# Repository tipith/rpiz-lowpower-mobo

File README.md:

# Motherboard

Purpose of this PCB is have a low-power way of sending SMS messages once an external trigger is detected. For example, it can be used as a an detector for door open events.

Features
- 18650 battery holder
- Attiny1604 power manager
- External trigger connector
- Nokia phone connector (FBUS + battery size indicator + battery temp)
- 2-way communication between PM and RPi

# Power manager (attiny1604)

tbd

# SMS sender (RPi Zero)

## Instructions

- /boot
   - add file: sshe
   - add file: wpa_supplicant.conf
   - add file: trapsms.ini
- /boot/config.txt
   - add "dtoverlay rpi3-disable-bt"
   - uncomment and modify "dtparam=i2c_arm=on,i2c_arm_baudrate=50000"
-  /boot/cmdline.txt
   - remove "console=serial0,115200 console=tty1"
- shell commands
   - sudo systemctl disable hciuart
   - sudo apt update && sudo apt upgrade
   - sudo apt install git gammu python3-gammu
- install pigpio
  - sudo apt-get install pigpio
  - wget https://raw.githubusercontent.com/joan2937/pigpio/master/util/pigpiod.service
  - sudo cp pigpiod.service /etc/systemd/system
  - sudo systemctl enable pigpiod.service
  - sudo systemctl start pigpiod.service
- run
   - python3 rpi_smssender/sms_sender.py

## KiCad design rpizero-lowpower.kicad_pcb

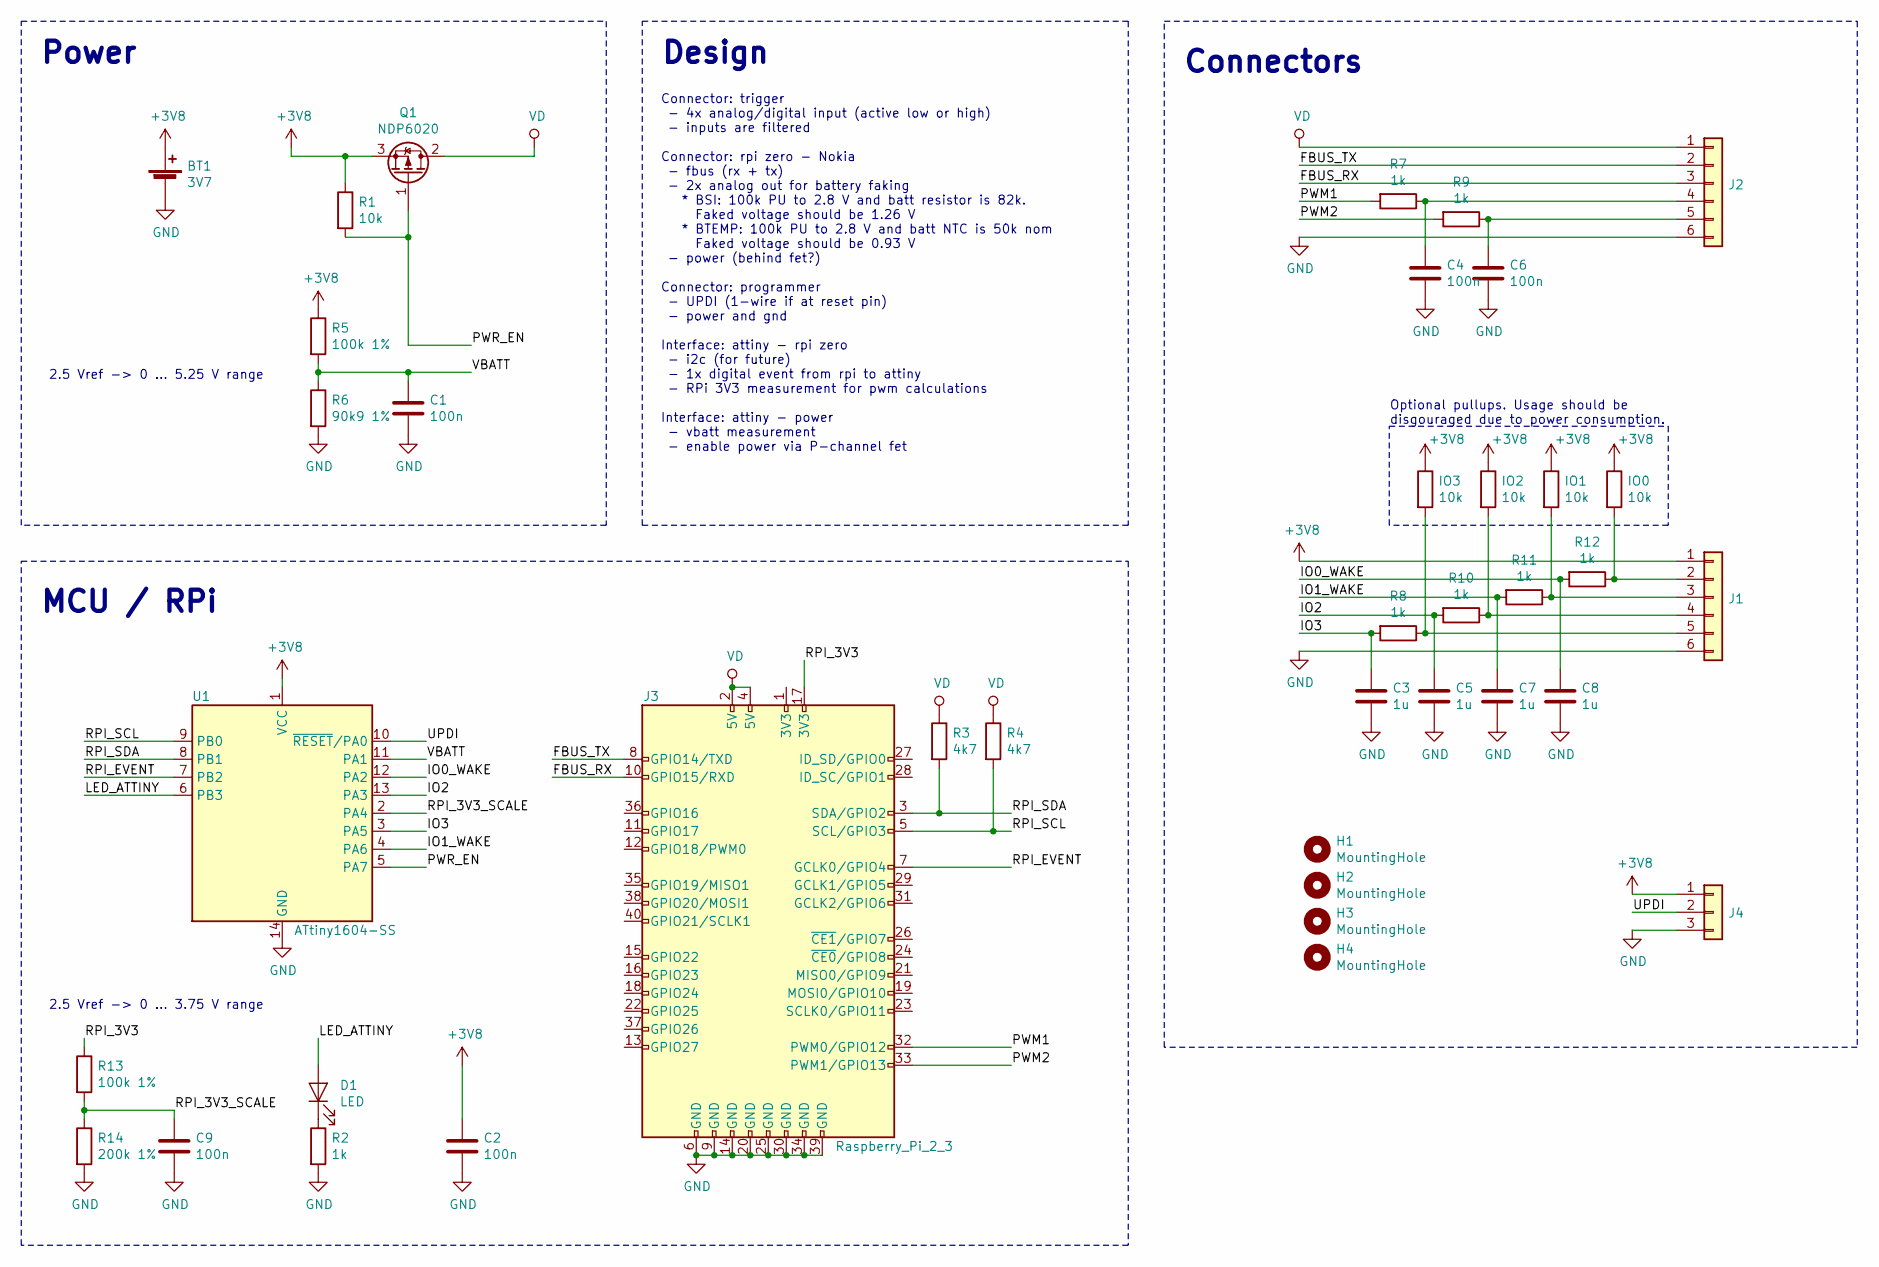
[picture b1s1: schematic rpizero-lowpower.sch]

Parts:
BT1: 3V7; 18650-ebay
C1, C2, C4, C6, C9: 100n; C_0805_2012Metric_Pad1.15x1.40mm_HandSolder
C3, C5, C7, C8: 1u; C_0805_2012Metric_Pad1.15x1.40mm_HandSolder
D1: LED; LED_0805_2012Metric_Pad1.15x1.40mm_HandSolder
H1, H2, H3, H4: MountingHole; MountingHole_5.3mm__no_courtyard
IO0, IO1, IO2, IO3: 10k; R_0805_2012Metric_Pad1.15x1.40mm_HandSolder
J1: Screw_Terminal_01x06; PinHeader_2x03_P2.54mm_Vertical
J2: Screw_Terminal_01x04; PinHeader_2x03_P2.54mm_Vertical
J3: Raspberry_Pi_2_3; Raspberry_Pi_Zero_Socketed_THT_FaceDown_MountingHoles_no_co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
J4: Conn_01x03; PinHeader_1x03_P2.54mm_Vertical
Q1: NDP6020; TO-220-3_Horizontal_TabDown
R1: 10k; R_0805_2012Metric_Pad1.15x1.40mm_HandSolder
R2, R7, R8, R9, R10, R11, R12: 1k; R_0805_2012Metric_Pad1.15x1.40mm_HandSolder
R3, R4: 4k7; R_0805_2012Metric_Pad1.15x1.40mm_HandSolder
R5, R13: 100k 1%; R_0805_2012Metric_Pad1.15x1.40mm_HandSolder
R6: 90k9 1%; R_0805_2012Metric_Pad1.15x1.40mm_HandSolder
R14: 200k 1%; R_0805_2012Metric_Pad1.15x1.40mm_HandSolder
U1: ATtiny1604-SS; SOIC-14_3.9x8.7mm_P1.27mm

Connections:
+3V8: BT1.1 (+), C2.1, IO0.1, IO1.1, IO2.1, IO3.1, J1.1, J4.1, Q1.3 (S), R1.1, R5.1, U1.1 (VCC)
/FBUS_RX: J2.3, J3.10 (GPIO15/RXD)
/FBUS_TX: J2.2, J3.8 (GPIO14/TXD)
/IO0_WAKE: C8.1, R12.2, U1.12 (PA2)
/IO1_WAKE: C7.1, R11.2, U1.4 (PA6)
/IO2: C5.1, R10.2, U1.13 (PA3)
/IO3: C3.1, R8.2, U1.3 (PA5)
/LED_ATTINY: D1.2 (A), U1.6 (PB3)
/PWM1: J3.32 (PWM0/GPIO12), R7.2
/PWM2: J3.33 (PWM1/GPIO13), R9.2
/PWR_EN: Q1.1 (G), R1.2, U1.5 (PA7)
/RPI_3V3: J3.17 (3V3), R13.1
/RPI_3V3_SCALE: C9.1, R13.2, R14.1, U1.2 (PA4)
/RPI_EVENT: J3.7 (GCLK0/GPIO4), U1.7 (PB2)
/RPI_SCL: J3.5 (SCL/GPIO3), R4.2, U1.9 (PB0)
/RPI_SDA: J3.3 (SDA/GPIO2), R3.2, U1.8 (PB1)
/UPDI: J4.2, U1.10 (~RESET~/PA0)
/VBATT: C1.1, R5.2, R6.1, U1.11 (PA1)
GND: BT1.2 (-), C1.2, C2.2, C3.2, C4.2, C5.2, C6.2, C7.2, C8.2, C9.2, J1.6, J2.6, J3.6 (GND), J3.9 (GND), J3.14 (GND), J3.20 (GND), J3.25 (GND), J3.30 (GND), J3.34 (GND), J3.39 (GND), J4.3, R2.2, R6.2, R14.2, U1.14 (GND)
unnamed: C4.1, J2.4, R7.1
unnamed: C6.1, J2.5, R9.1
unnamed: D1.1 (K), R2.1
unnamed: IO0.2, J1.2, R12.1
unnamed: IO1.2, J1.3, R11.1
unnamed: IO2.2, J1.4, R10.1
unnamed: IO3.2, J1.5, R8.1
VD: J2.1, J3.2 (5V), J3.4 (5V), Q1.2 (D), R3.1, R4.1

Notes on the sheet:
Connector: trigger - 4x analog/digital input (active low or high) - inputs are filtered Connector: rpi zero - Nokia - fbus (rx + tx) - 2x analog out for battery faking * BSI: 100k PU to 2.8 V and batt resistor is 82k. Faked voltage should be 1.26 V * BTEMP: 100k PU to 2.8 V and batt NTC is 50k nom 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
Power
MCU / RPi
Connectors
Design
Optional pullups. Usage should be disgouraged due to power consumption.
2.5 Vref -> 0 ... 5.25 V range
2.5 Vref -> 0 ... 3.75 V range

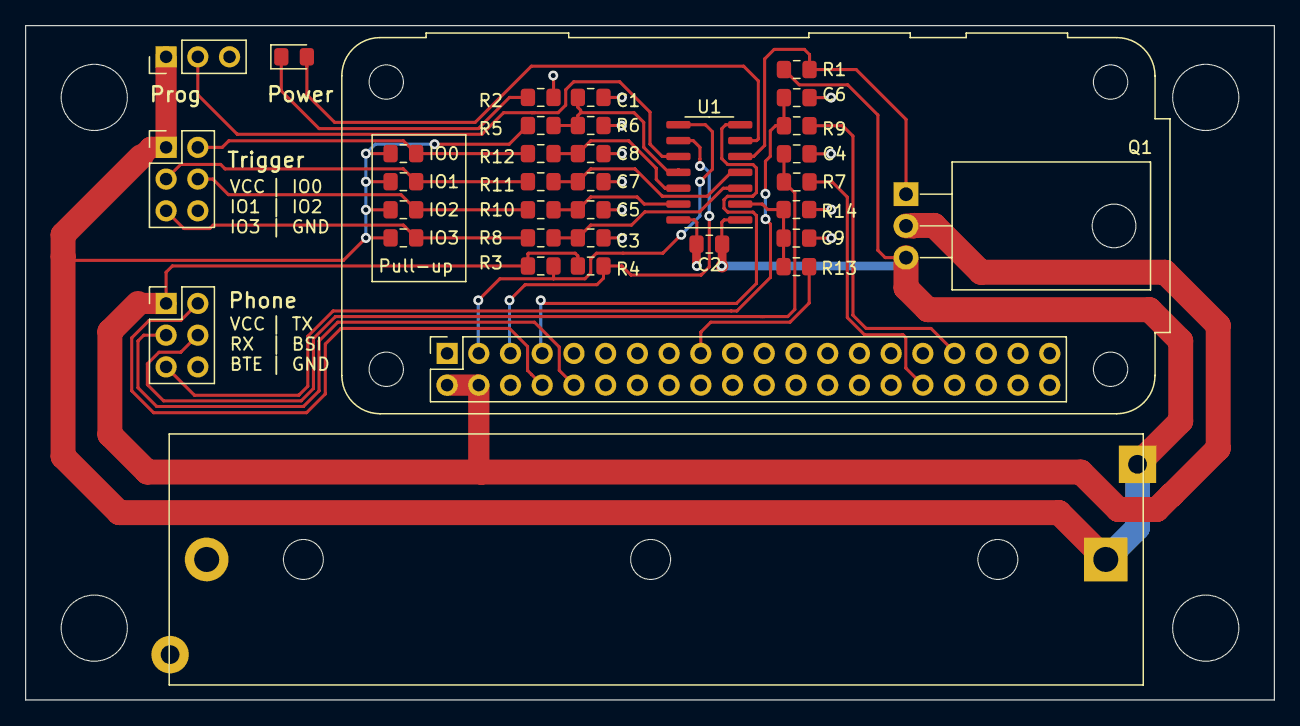
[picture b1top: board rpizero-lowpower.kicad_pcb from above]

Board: 2 copper layers, 100.0 x 54.0 mm, 39 parts (0 on the bottom side), 27 nets.

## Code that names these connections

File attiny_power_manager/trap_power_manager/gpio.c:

/*
 * io.c
 *
 * Created: 30/06/2019 21.23.41
 *  Author: pihlstro
 */ 
#include <avr/io.h>
#include <avr/interrupt.h>

#include "gpio.h"

struct gpio_context {
	onPinTransitionFunc cb;
};

static struct gpio_context gpio[PIN_NUM];

ISR(PORTA_PORT_vect)
{
	if (PORTA.INTFLAGS & PORT_INT2_bm)
	{
		PORTA.INTFLAGS = PORT_INT2_bm;
		if (gpio[PIN_IO0].cb)
		{
			gpio[PIN_IO0].cb();
		}
	}
	
	if (PORTA.INTFLAGS & PORT_INT6_bm)
	{
		PORTA.INTFLAGS = PORT_INT6_bm;
		if (gpio[PIN_IO1].cb)
		{
			gpio[PIN_IO1].cb();
		}
	}
	
	reti();
}

ISR(PORTB_PORT_vect)
{
	if (PORTA.INTFLAGS & PORT_INT2_bm)
	{
		PORTA.INTFLAGS = PORT_INT2_bm;
		if (gpio[PIN_RPI_EVENT].cb)
		{
			gpio[PIN_RPI_EVENT].cb();
		}
	}
	
	reti();
}

void gpio_init(void)
{
	/* PA0 - UPDI
	 * PA1 - VBATT    - analog in
	 * PA2 - IO0_WAKE - digital in, async isr 
	 * PA3 - IO2      - digital in/out
	 * PA4 - RPI_3V3  - analog in
	 * PA5 - IO3      - digital in/out
	 * PA6 - IO1_WAKE - digital in, async isr
	 * PA7 - PWR_EN   - digital out */
	PORTA.DIRSET = 0b10101000;
	PORTA.PIN1CTRL = PORT_ISC_INPUT_DISABLE_gc;
	PORTA.PIN2CTRL = PORT_ISC_FALLING_gc;
	PORTA.PIN3CTRL = PORT_ISC_INPUT_DISABLE_gc;
	PORTA.PIN6CTRL = PORT_ISC_FALLING_gc;
	
	/* PB0 - RPI_SCL   - i2c slave
	 * PB1 - RPI_SCA   - i2c slave
	 * PB2 - RPI_EVENT - digital in, async isr
	 * PB3 - LED       - digital out */
	PORTB.DIRSET = 0b1011;
	PORTB.PIN2CTRL = PORT_ISC_FALLING_gc;
}

void gpio_subscribe(enum iopin pin, onPinTransitionFunc cb)
{
	gpio[pin].cb = cb;
}

void gpio_set(enum iopin pin)
{
	switch (pin)
	{
	case PIN_IO2:
		PORTA.OUTSET = (1 << 3);
		break;
	case PIN_IO3:
		PORTA.OUTSET = (1 << 5);
		break;
	case PIN_PWR_EN:
		PORTA.OUTSET = (1 << 7);
		break;
	case PIN_LED:
		PORTB.OUTSET = (1 << 3);
		break;
	case PIN_SCL:
		PORTB.OUTSET = (1 << 0);
		break;
	case PIN_SDA:
		PORTB.OUTSET = (1 << 1);
		break;
	default:
		break;
	}
}

void gpio_clear(enum iopin pin)
{
	switch (pin)
	{
	case PIN_IO2:
		PORTA.OUTCLR = (1 << 3);
		break;
	case PIN_IO3:
		PORTA.OUTCLR = (1 << 5);
		break;
	case PIN_PWR_EN:
		PORTA.OUTCLR = (1 << 7);
		break;
	case PIN_LED:
		PORTB.OUTCLR = (1 << 3);
		break;
	case PIN_SCL:
		PORTB.OUTCLR = (1 << 0);
		break;
	case PIN_SDA:
		PORTB.OUTCLR = (1 << 1);
		break;
	default:
		break;
	}
}

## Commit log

2019-07-19 rev1
2019-07-19 add documentation
2019-07-19 bom updated with mouser part numbers
2019-07-27 add power manager and refactor into directories
2019-07-28 add i2c communication between attiny and rpi zero
2019-07-30 add temperature register
2019-07-31 vs code tooling for attiny development
2019-07-31 vs code dev env updates
2019-07-31 state pattern implementation with actual classes
2019-08-03 logging via i2c
2019-08-04 sleep mode
2019-08-05 method to request speedier shutdown
2019-08-06 logging for sms sender
